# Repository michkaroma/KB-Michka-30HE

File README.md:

# KB-Michka-30HE

Clavier mécanique custom ultra-compact de 30 touches à effet Hall, filaire, pour la main gauche (demi-clavier gaming). Conçu de zéro, de la génération du PCB avec Ergogen jusqu'au routage dans KiCad.

Projet inspiré et adapté du [Lucca-58HE](https://github.com/Maka8295) de Maka8295, avec des choix de conception différents (MCU, mux, firmware, filtrage par touche). Le schéma d'alimentation s'appuie sur l'étude du projet HE60.

## Caractéristiques

- **30 touches** : matrice 6×4 + 5 touches de pouce + 1 touche isolée
- **Disposition** : AZERTY
- **Switches analogiques** à effet Hall avec capteur intégré
- **Filaire** (USB-C via le MCU)
- **Firmware** : KMK (CircuitPython)

## Composants principaux

| Rôle | Composant | Notes |
|---|---|---|
| Switches | Gateron Magnetic Jade PRO HE | Capteur Hall intégré, pôle N face au PCB, entraxe 10 mm |
| MCU | Waveshare RP2040-Zero | Régulateur 3.3 V embarqué, ADC sur GP27 |
| Multiplexeur | ADG732 (TQFP) | Analogique 32 canaux, adressé sur 5 bits |
| Ferrite | Perle 600 Ω @ 100 MHz, boîtier 0805 | Sépare le rail analogique du rail numérique |

### Affectation des GPIO (RP2040-Zero)

| GPIO | Fonction |
|---|---|
| GP0–GP4 | Lignes d'adresse du mux (MUX_A4 → MUX_A0) |
| GP27 | Entrée ADC (AIN1, sortie commune du mux) |

Les entrées de contrôle CS, WR et EN de l'ADG732 sont câblées à GND (mux toujours actif, sélection purement par adresse).

## Architecture électrique

### Alimentation : rail analogique 3V3A

Le RP2040-Zero ne fournit qu'une seule sortie 3.3 V. Le rail analogique est donc dérivé du rail numérique à travers une ferrite, avec un filtre en pi :

```
RP2040-Zero 3V3 ──┬──── ferrite 600Ω ────┬──── 3V3A ──→ capteurs + ADG732
                  │                      │
             10µF + 100nF           10µF + 100nF
                  │                      │
                 GND                    GND
```

La ferrite laisse passer le courant continu (~0.3 Ω en DC) mais présente 600 Ω à 100 MHz : le bruit de commutation du MCU ne remonte pas dans le rail des capteurs. Les condensateurs sont en dérivation (un pad sur le rail, un pad vers GND) ; seule la ferrite est en série. Le plan de masse reste commun (un seul GND, pas de masse analogique séparée).

À la différence du HE60, qui utilise deux régulateurs LDO distincts (TLV75733 pour le numérique, XC6206 pour l'analogique), l'approche ferrite est adaptée ici au fait que le RP2040-Zero embarque déjà son régulateur.

### Filtrage par touche

Chaque touche embarque ses passifs directement dans le footprint custom `HESwitch_Michka`, ce qui garantit leur proximité avec le capteur :

```
3V3A ──┬──→ VCC capteur
       │
     100nF                     capteur ──→ 1kΩ ──┬──→ vers ADG732
       │                                         │
      GND                                      4.7nF
                                                 │
                                                GND
```

- **100 nF** (X7R) : découplage de l'alimentation du capteur
- **1 kΩ + 4.7 nF** (C0G/NP0 de préférence) : filtre RC passe-bas sur la sortie analogique, fc ≈ 34 kHz — le signal d'appui (quelques centaines de Hz) passe intact, le bruit HF est atténué

Le filtre est placé **par capteur, en amont du mux** : chaque nœud est déjà stabilisé quand le mux le sélectionne, ce qui évite les problèmes de temps d'établissement pendant le scan. La résistance série isole en plus le capteur du transitoire de charge à chaque commutation de canal. (Le HE60 n'a que le condensateur shunt, sans résistance série.)

### Récapitulatif des valeurs

| Emplacement | Composant | Valeur | Quantité |
|---|---|---|---|
| Filtre pi, côté MCU | Condensateur 0805 | 10 µF + 100 nF | 1 + 1 |
| Filtre pi, côté 3V3A | Condensateur 0805 | 10 µF + 100 nF | 1 + 1 |
| Entre les deux | Ferrite 0805 | 600 Ω @ 100 MHz | 1 |
| Par touche, découplage | Condensateur | 100 nF | 30 |
| Par touche, filtre sortie | Résistance | 1 kΩ | 30 |
| Par touche, filtre sortie | Condensateur | 4.7 nF | 30 |

## Toolchain et méthode

1. **Ergogen v4.2.1** (npm) génère le placement des touches et le PCB initial à partir de `ergogen/layout.yaml`, avec des footprints custom en JavaScript :
   - `HESwitch_Michka.js` — switch HE avec passifs intégrés (pads GND, VCC, signal externe vers le mux, signal interne Q du capteur)
   - `ADG732.js` — mux TQFP
   - `RP2040_Zero.js` — MCU
   - `C0805.js` — condensateur 0805 (converti depuis un `.kicad_mod`)
   - `mountinghole.js` — trous de fixation M2
2. **Script Python de post-traitement** : Ergogen 4.2.1 génère les arcs (`gr_arc`) à l'ancien format `(start)(end)(angle)` alors que KiCad 10 exige `(start)(mid)(end)`. Le script calcule mathématiquement le point `mid` de chaque arc.
3. **KiCad 10** : reprise du PCB généré (`kicad/pcb/`), placement final et routage.

### Ordre de routage prévu

1. Pour de masse GND
2. Rails d'alimentation (3V3 puis 3V3A)
3. Pistes de contrôle numériques vers l'ADG732 (adresses)
4. Pistes analogiques en dernier, courtes et éloignées des signaux bruyants

## État d'avancement

- [x] Layout Ergogen (outlines + placement des 30 touches)
- [x] Footprints custom (switch, mux, MCU, condensateur, fixations)
- [x] Pipeline Ergogen → KiCad 10 (conversion des arcs)
- [x] Placement du filtre d'alimentation près du MCU
- [x] Routage de la rangée r1 (signaux, alimentation, capteurs)
- [ ] Création du net 3V3A en aval de la ferrite
- [ ] Routage des rangées r2–r5 et des touches de pouce
- [ ] Pour de masse
- [ ] Annotation des références (C*, R*, FB1, U*)
- [ ] Firmware KMK

## Structure du dépôt

```
ergogen/
  layout.yaml        # Source de vérité du layout
  footprints/        # Footprints custom (JS)
  output/            # Outlines DXF + PCB généré
kicad/
  pcb/               # Projet KiCad 10 (placement + routage)
```

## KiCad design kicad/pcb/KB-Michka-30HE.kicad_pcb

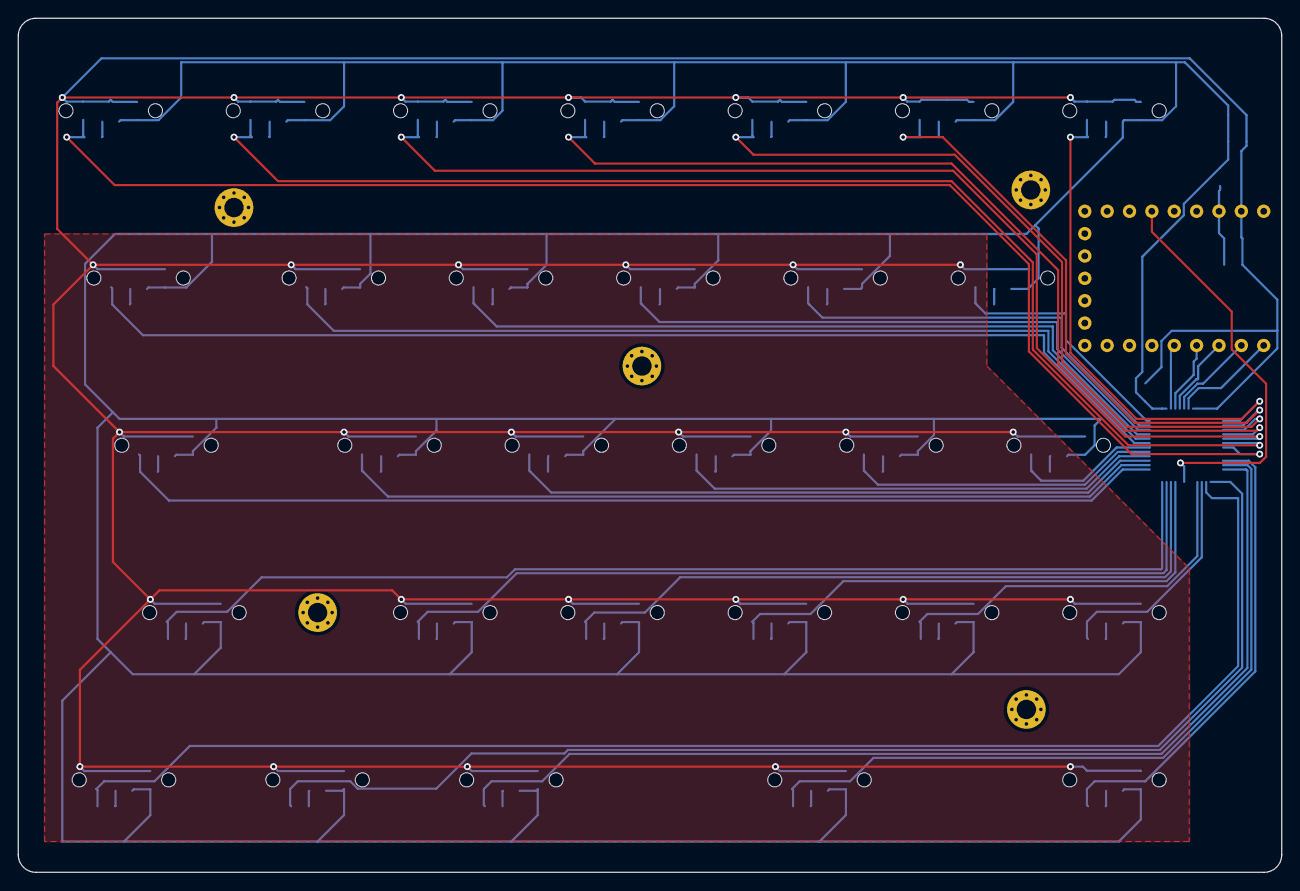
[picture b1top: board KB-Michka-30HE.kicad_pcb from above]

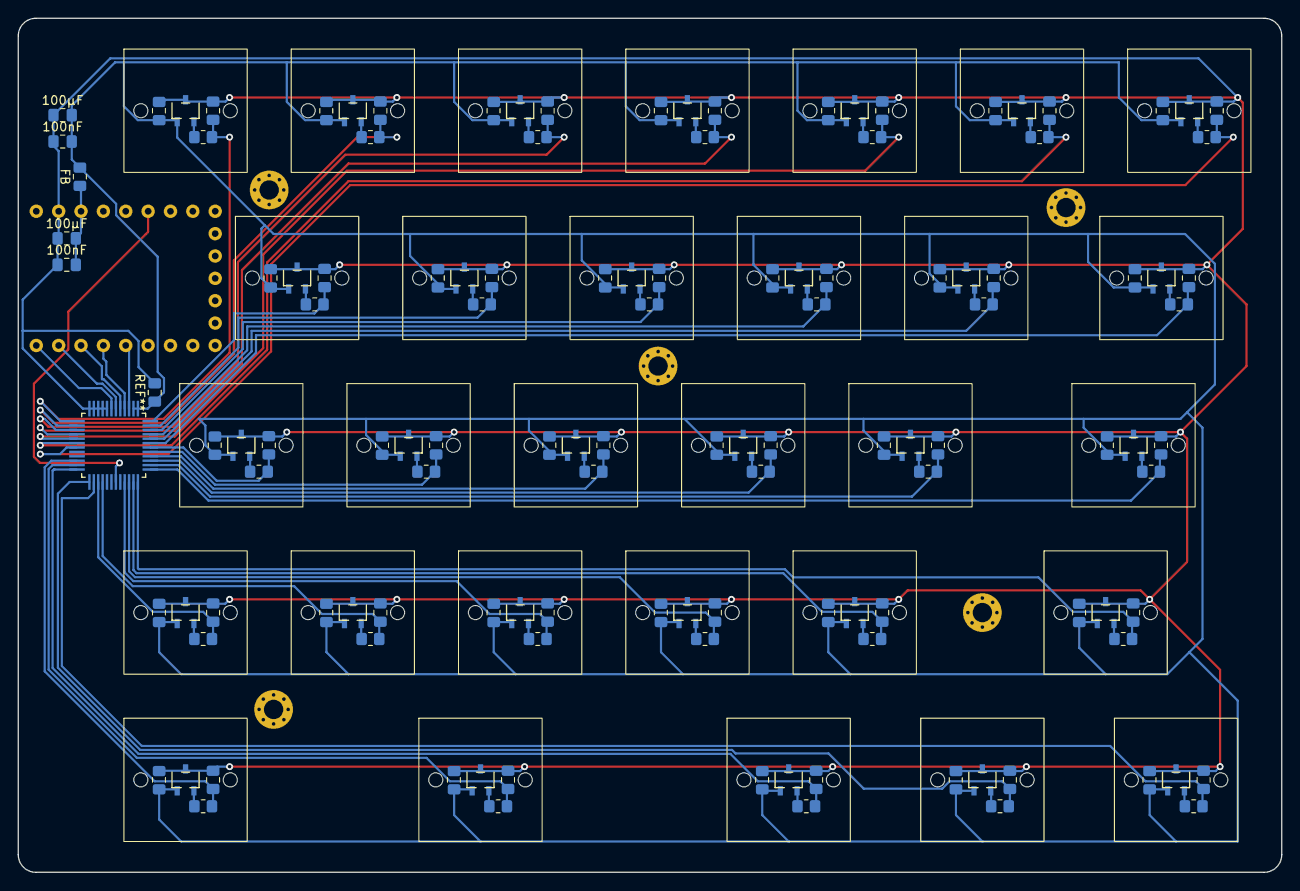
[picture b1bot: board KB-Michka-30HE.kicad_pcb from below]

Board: 2 copper layers, 143.5 x 97.0 mm, 10 parts (5 on the bottom side), 3 nets.

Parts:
100nF, 100nF#2, 100µF, 100µF#2: C_0805_2012Metric_Pad1.18x1.45mm_HandSolder
FB: C_0805_2012Metric_Pad1.18x1.45mm_HandSolder
_1, _2, _3, _4, _5: MountingHole_2.2mm_M2_Pad_Via

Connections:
3V3A: 100nF.2, 100µF.2, FB.2
GND: 100nF.1, 100nF#2.1, 100µF.1, 100µF#2.1
VCC: 100nF#2.2, 100µF#2.2, FB.1

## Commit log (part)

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2026-04-20 ergogen
2026-04-20 perfection du layout
2026-04-20 outlines-ergogen
2026-04-20 début du pcb
2026-04-20 add gitignore
2026-04-20 avance du pcb
2026-04-21 avancement du pcb sur ergogen
2026-04-21 début kicad
2026-04-21 ajout des trous de vis
2026-04-21 ajustement de la footprint
2026-04-21 ADG732 ergogen
2026-04-21 réinitialisation du pcb
2026-04-22 ajustement du layout mcu et mux ergogen
2026-05-19 suppression des net des screws
2026-05-19 miroir y ADG732/arangement.py/mv footprint footprints
2026-05-20 connexion mux
